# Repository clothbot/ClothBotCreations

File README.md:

ClothBotCreations
=================

Original creations for demos &amp; workshops.

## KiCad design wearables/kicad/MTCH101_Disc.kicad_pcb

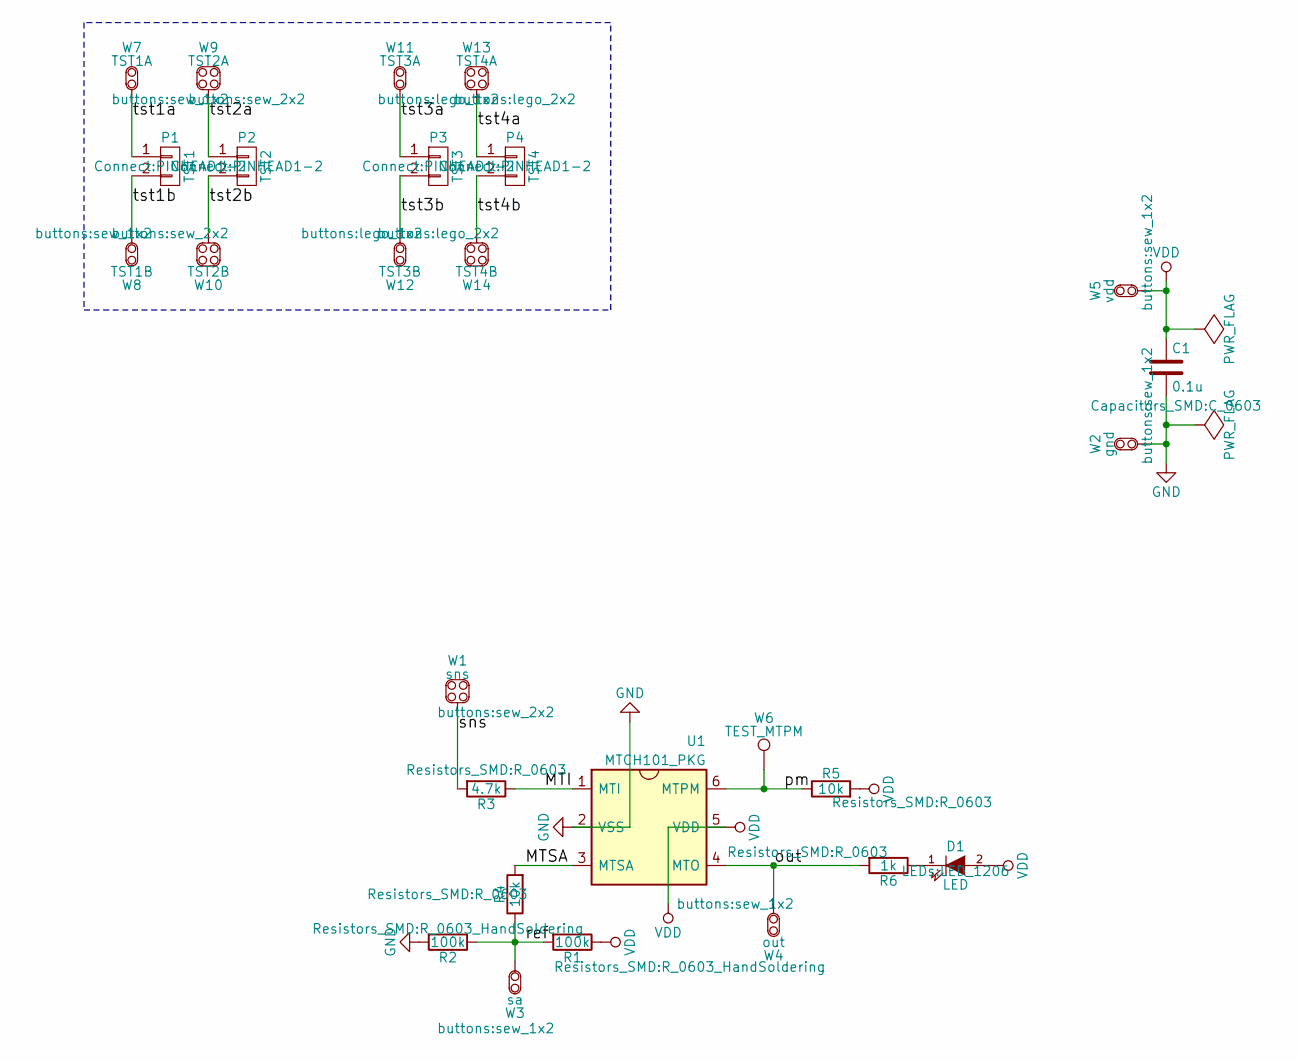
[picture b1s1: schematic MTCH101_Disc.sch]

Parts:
C1: 0.1u; C_0603
D1: LED; LED_1206
P1: TST1; PINHEAD1-2
P2: TST2; PINHEAD1-2
P3: TST3; PINHEAD1-2
P4: TST4; PINHEAD1-2
R1, R2: 100k; R_0603_HandSoldering
R3: 4.7k; R_0603
R4, R5: 10k; R_0603
R6: 1k; R_0603
U1: MTCH101_PKG; SOT-23-6; PartName MTCH101
W1: sns; sew_2x2
W2: gnd; sew_1x2
W3: sa; sew_1x2
W4: out; sew_1x2
W5: vdd; sew_1x2
W6: TEST_MTPM; Measurement_Point_Round-SMD-Pad_Small
W7: TST1A; sew_1x2
W8: TST1B; sew_1x2
W9: TST2A; sew_2x2
W10: TST2B; sew_2x2
W11: TST3A; lego_1x2
W12: TST3B; lego_1x2
W13: TST4A; lego_2x2
W14: TST4B; lego_2x2

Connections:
/MTI: R3.1, U1.1 (MTI)
/MTSA: R4.2, U1.3 (MTSA)
/out: R6.2, U1.4 (MTO), W4.1
/pm: R5.1, U1.6 (MTPM), W6.1
/ref: R1.2, R2.1, R4.1, W3.1
/sns: R3.2, W1.1
/tst1a: P1.1, W7.1
/tst1b: P1.2, W8.1
/tst2a: P2.1, W9.1
/tst2b: P2.2, W10.1
/tst3a: P3.1, W11.1
/tst3b: P3.2, W12.1
/tst4a: P4.1, W13.1
/tst4b: P4.2, W14.1
GND: C1.2, R2.2, U1.2 (VSS), W2.1
unnamed: D1.1 (K), R6.1
VDD: C1.1, D1.2 (A), R1.1, R5.2, U1.5 (VDD), W5.1

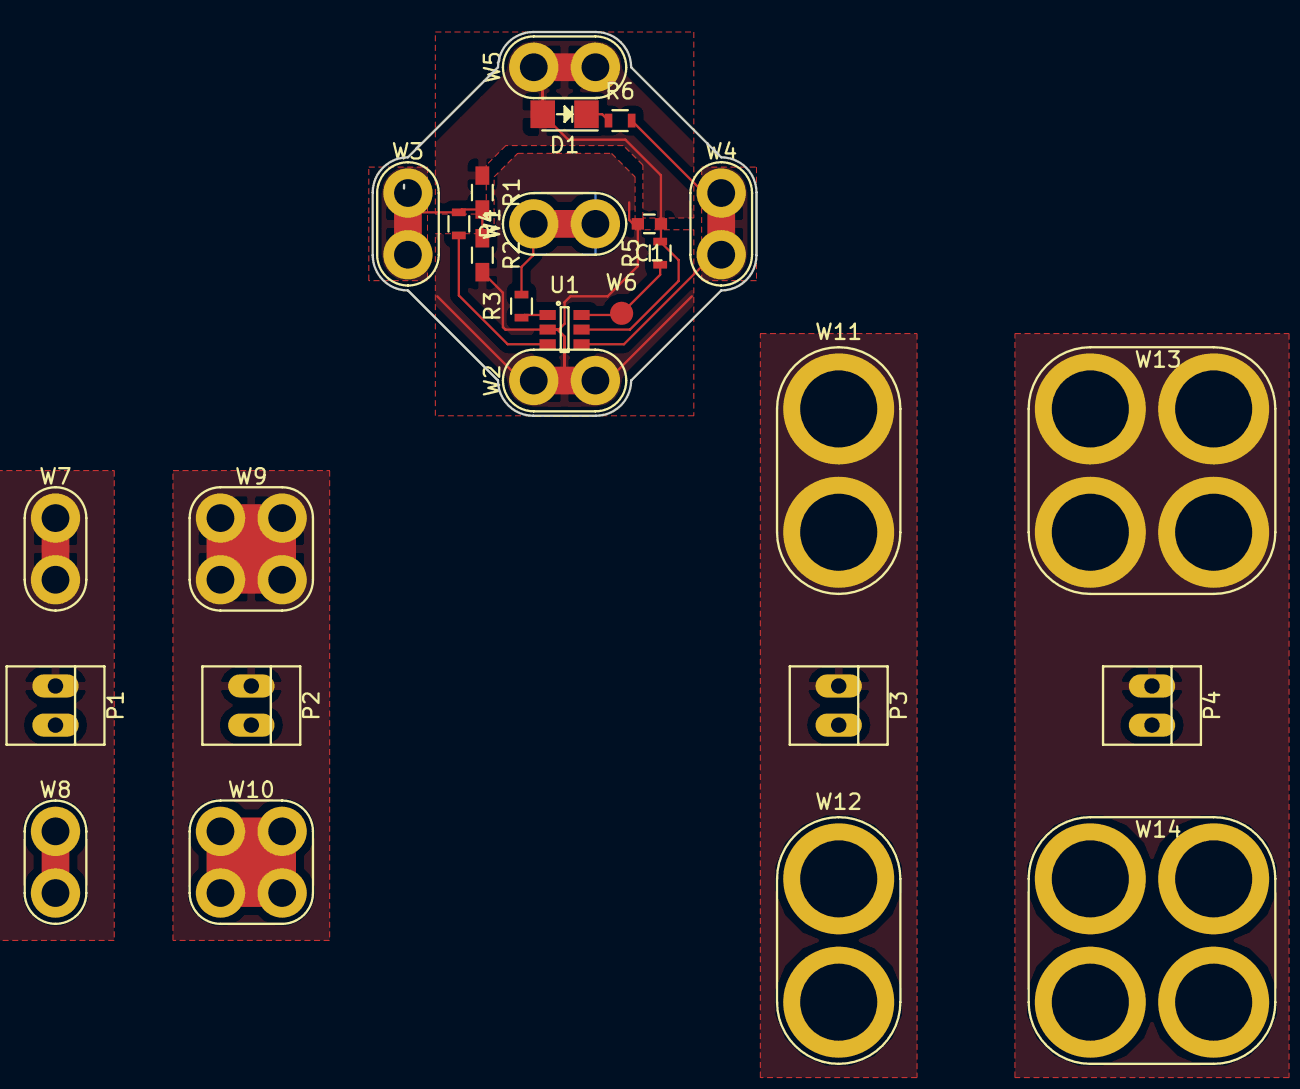
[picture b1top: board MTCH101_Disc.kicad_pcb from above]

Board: 2 copper layers, 24.9 x 24.9 mm, 27 parts (0 on the bottom side), 17 nets.

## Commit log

2013-07-21 Initial commit.
2013-07-21 Deleted derived files.
2013-08-06 WIP.
2013-08-09 more WIP...
2013-08-27 Broke out butterfly_2d to simplify.
2013-08-27 Added some useful functions and modules.
2013-08-28 More WIP.
2013-08-28 More WIP. Almost got the tail parts working.
2013-08-28 Mostly works. Includes offset for printing with RHS tool head.
2013-08-29 Tweaks.
2013-08-29 Reworking for Ditto printing.
2013-08-30 Initial add.
2013-08-30 Clean-up of relative peg heights.
2013-08-31 Cleaning up filled variant.
2013-08-31 Added filled variant.
2014-05-19 Catching up.
2014-05-19 Fillet example.
2014-05-19 Break out offset_3d() function for optimization.
2014-05-22 Initial add of intersection_iterators examples.
2014-05-22 Typo.
2014-05-23 Hypothetical example of 3D offset and explode iteration.
2014-05-23 Added solid argument.
2014-12-15 Testing new null() operations in latest OpenSCAD
2014-12-15 Alternate pos/neg space masking.
2014-12-15 Testing variations on grid matching.
2014-12-15 More efficient grid_match example.
2014-12-15 Added ca_2x2_grid_map example.
2014-12-15 Exercise union of multiple pattern matches.
2014-12-16 Sync up CR/LF.
2014-12-16 New hex_mappings tests.
2014-12-16 Sync up.
2014-12-17 Initial commit of corner_relief experiment
2014-12-17 Added corner_relief mode="round" for acute cases.
    For simple perpendicular geometry mode="miter" is sufficient and likely
    faster. For acute angle cases, mode="round" is more accurate.
2014-12-17 Add compensation factor to corner_relief
2014-12-27 Geometrically finding geometry that fails a "thinner" check.
2014-12-27 Slightly more elaborate example.
2014-12-27 Renamed offset_3d to inner_offset_3d since it's only offsets inwards.
2015-01-01 Work in progress.
2015-01-01 work in progress
2015-01-05 Refactored LCBM and new utilities files.
2015-01-18 Initial commit of watch strap stuff.
2015-01-20 Variant work in progress.
2015-01-23 Expanding ideas.
2015-01-25 Expanding complex case and handling r=0 case.
2015-01-25 Chain link variation.
2015-01-25 Tweaked axles.
2015-07-05 minkowski_null module added
    Hack to map minkowski of 0-volume children to null.
2015-07-14 Sphere experiments.
2015-07-15 DFM tweaks.
2015-07-15 More DFM tweaks.
2015-07-15 More tweaks to hole cutout.
2015-07-16 Progress.
    Just fits, but needs rework on the latching mechanism.
2015-07-19 Modified latching mechanism for better performance
2015-07-20 Tweaking the relative layer thicknesses.
2015-07-25 Issue #1400 test
    Testing auto-reload of variables and other dependencies. Filed issue
    #1400 for surface(“surface.dat”) changes not detected.
2015-07-26 Adding a little variety.
2015-07-28 Directional minkowski experiment.
2015-07-28 Added scale_d parameter.
2015-07-28 added some animation fun
2015-08-03 Directed Minkowski Experiments
2015-08-03 Simplified bulge_cone()
2015-08-03 Added spherical coordinate directions
2015-08-03 Added spherical to bulge_cube()
2015-08-04 Added spherical coordinates.
2015-08-04 Modified children iterator for future optimization.
2015-08-10 Color left/red, right/green
2015-08-26 Shapeways CustomMaker Test
    Work in progress.
2015-11-16 Initial add of linear_algebra play.
2015-12-25 Initial checkin of my old Faceplate clip design
2015-12-25 Initial checkin
    Derived from http://www.thingiverse.com/thing:28241/
2015-12-26 Symmetry tweak
    Made the idler symmetric and positioned to allow dual-extrusion at 32mm
    separation.
2015-12-26 Modified peg centre hole for screw
2015-12-26 Redesigned symmetry and plating
    Symmetric base and idler. Plated to allow for dual-extrusion printing
    two at once.
2015-12-26 Forgot about clearances. Fixed.
2016-01-20 hypothetical example for issue 1562
2016-01-21 Testing pointset() primitive.
2016-01-21 More testing.
2016-01-21 Tweaks to read_xyz().
2016-01-21 Simple boolean and invalid file test.
2016-01-24 Cleaned up examples
2016-03-11 concave_support example
2016-03-11 convex_decomposition faked
2016-03-14 electrical tests - WIP
2016-03-29 Added text projection example.
2016-03-29 Projected text via directed minkowski
2016-03-29 Grid example
2016-03-29 grid mapping example.
2016-10-18 Dabbling with kicad
    Refreshing my memory before diving into a proper project.
2016-10-18 ignore .bck files
2016-10-19 more exploration
2016-10-20 Creating button connector library
2016-10-20 tweaks
2016-10-20 variants
2016-10-20 reworking.
2016-10-21 exploring vdd/gnd routing options
2016-10-21 more seweable terminal variants
2016-10-21 more dabbling
2016-11-05 More misc play.
2017-10-25 Playing with fonts
